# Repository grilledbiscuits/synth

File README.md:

# Fully Analog Synthesizer Passion Project

> This repository documents some of the work I have done starting in 2024 on
> this project.

I have tried to include as many schematics as possible. The schematics are
mainly just for documentation's sake, as it is rather difficult to simulate the
constantly-changing signals involved in these circuits. I haven't been able to
order a PCB for any of the modules designed here for cost-related issues but I
intend to keep working on this project to polish it to the best of my ability.

---

## Modules

Every module lives as its own sheet in the
[`synth-allmodules`](KiCAD/current-modules/synth-allmodules) KiCad project, with
the reference circuit it was designed from kept in
[`KiCAD/references`](KiCAD/references).

| Module | Based on | Reference |
| --- | --- | --- |
| ADSR | Kassutronics Precision ADSR (Eddy Bergman version) | [image](KiCAD/references/ADSR) |
| 8 Step Sequencer | [Eddy Bergman, 8 Step Sequencer v2.1](https://www.eddybergman.com/2019/12/synthesizer-build-part-8-8-step.html) | [image](KiCAD/references/8stepsequencer) |
| Bass | Thomas Henry, Bass++ | [image](KiCAD/references/bass) |
| LFO | Ken Stone, CGS58 Utility LFO | [image](KiCAD/references/LFO) |
| VCA | Thomas Henry, VCA-1 | [image](KiCAD/references/VCA) |
| VCF-1 | [Thomas Henry, VCF-1 State Variable Filter](https://www.eddybergman.com/2024/04/THVCF1statevariablefilter.html) | [image](KiCAD/references/VCF-1) |
| VCF-2 | [YuSynth, Steiner-Parker Diode Filter](https://www.eddybergman.com/2021/12/synthersizer-build-part-45-steiner.html) | [image](KiCAD/references/VCF-2) |
| VCO | Thomas Henry, X-4046 VCO | [image](KiCAD/references/VCO) |
| 808 Kick | [Juanito Moore, 808 Kick](https://www.eddybergman.com/2021/12/synthesizer-build-part-46-808-kick-for.html) | [image](KiCAD/references/808kick) |

## Repository Layout

```
KiCAD/
├── current-modules/
│   ├── synth-allmodules/   # main project, one sheet per module
│   └── 8stepsequencer/     # standalone sequencer project
├── references/             # reference schematics, one folder per module
├── Library/                # custom symbols and footprints
└── DEPRECATED/             # older designs, kept for reference
SPICE Models/
SLDWRKS (DEPRECATED)/
```

To open the schematics, load
`KiCAD/current-modules/synth-allmodules/synth-allmodules.kicad_pro` in KiCad 10.

---

## Core Concepts

This project is going to require us to expand our current level of
understanding of the following areas of electronic engineering:

- Soldering skills
- PCB design
- Analog Signals
- Schematics

## To-Do

- [x] Initialise a repo
- [x] Start up a README
- [ ] Update all schematics
- [ ] Start with CAD design of housings
- [ ] Add mute switches to the sequencer!
- [ ] Add an amplifier
- [ ] Plenty of other things, no doubt

## Possible Cool Features

These are just me spitballing crazy ideas. None of these really have anything
to do with the base project but it would be cool if we could look into these
somewhat:

- More LEDs for better visual feedback
- Some cheap screens to watch the signals
- Increased modularity and uniform housings
- More modules!
- Portable version???

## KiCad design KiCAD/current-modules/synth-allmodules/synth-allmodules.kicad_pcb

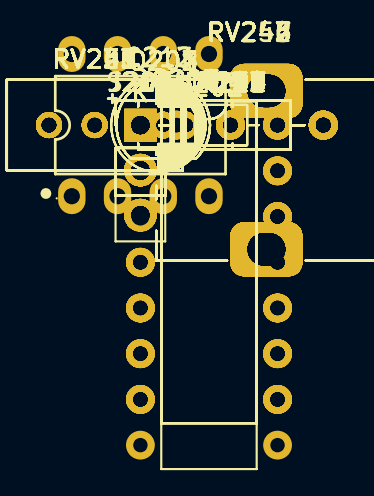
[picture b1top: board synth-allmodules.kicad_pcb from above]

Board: 2 copper layers, 93 parts (0 on the bottom side), 63 nets, no tracks yet.

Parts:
C201: 100p; C_Disc_D5.0mm_W2.5mm_P5.00mm
C202: 470p; C_Disc_D5.0mm_W2.5mm_P5.00mm
C203, C204, C205, C206, C207, C208, C209: 10n; C_Disc_D5.0mm_W2.5mm_P5.00mm
C210: 100n; C_Disc_D5.0mm_W2.5mm_P5.00mm
C211: 220n; C_Disc_D5.0mm_W2.5mm_P5.00mm
C212, C213: 10u; CP_Radial_D5.0mm_P2.00mm
D201, D202, D203: 1N4148; D_DO-35_SOD27_P7.62mm_Horizontal
J201: 1V/OCT; PinHeader_1x02_P2.54mm_Vertical
J202: EXP FM; PinHeader_1x02_P2.54mm_Vertical
J203: LIN FM; PinHeader_1x02_P2.54mm_Vertical
J204: HARD SYNC; PinHeader_1x02_P2.54mm_Vertical
J205: TRIANGLE; PinHeader_1x02_P2.54mm_Vertical
J206: RAMPOID; PinHeader_1x02_P2.54mm_Vertical
J207: SAW; PinHeader_1x02_P2.54mm_Vertical
J208: PWM; PinHeader_1x02_P2.54mm_Vertical
J209: SINE; PinHeader_1x02_P2.54mm_Vertical
J210: PULSE; PinHeader_1x02_P2.54mm_Vertical
J211: +12 / GND / -12; PinHeader_1x03_P2.54mm_Vertical
Q201, Q202, Q203, Q204, Q205: 2N3904; TO-92_Inline
R202, R203: 390R; R_Axial_DIN0207_L6.3mm_D2.5mm_P10.16mm_Horizontal
R204, R205, R206, R207: 1k; R_Axial_DIN0207_L6.3mm_D2.5mm_P10.16mm_Horizontal
R208, R210, R211, R212, R213: 2.2k; R_Axial_DIN0207_L6.3mm_D2.5mm_P10.16mm_Horizontal
R209: 2k; R_Axial_DIN0207_L6.3mm_D2.5mm_P10.16mm_Horizontal
R214: 4.7k; R_Axial_DIN0207_L6.3mm_D2.5mm_P10.16mm_Horizontal
R215, R216, R217: 10k; R_Axial_DIN0207_L6.3mm_D2.5mm_P10.16mm_Horizontal
R218, R219: 15k; R_Axial_DIN0207_L6.3mm_D2.5mm_P10.16mm_Horizontal
R220: 12k; R_Axial_DIN0207_L6.3mm_D2.5mm_P10.16mm_Horizontal
R221: 18k; R_Axial_DIN0207_L6.3mm_D2.5mm_P10.16mm_Horizontal
R222: 33k; R_Axial_DIN0207_L6.3mm_D2.5mm_P10.16mm_Horizontal
R224, R225, R226: 75k; R_Axial_DIN0207_L6.3mm_D2.5mm_P10.16mm_Horizontal
R227, R228, R229, R230, R231, R232, R233, R234, R235: 100k; R_Axial_DIN0207_L6.3mm_D2.5mm_P10.16mm_Horizontal
R248, R249: 120k; R_Axial_DIN0207_L6.3mm_D2.5mm_P10.16mm_Horizontal
R250, R251, R252: 220k; R_Axial_DIN0207_L6.3mm_D2.5mm_P10.16mm_Horizontal
R254: 1.5M; R_Axial_DIN0207_L6.3mm_D2.5mm_P10.16mm_Horizontal
R255: 2.2M; R_Axial_DIN0207_L6.3mm_D2.5mm_P10.16mm_Horizontal
R256: 3.3M; R_Axial_DIN0207_L6.3mm_D2.5mm_P10.16mm_Horizontal
RV201: 100R; Potentiometer_Bourns_3296W_Vertical
RV223: 50k; Potentiometer_Bourns_3296W_Vertical
RV236, RV237, RV238, RV239, RV240, RV241: 100k; Potentiometer_Bourns_3296W_Vertical
RV242, RV243, RV244, RV245, RV246, RV247: 100k; Potentiometer_Alps_RK09K_Single_Vertical
RV253: 500k; Potentiometer_Alps_RK09K_Single_Vertical
S201: AC/DC; PinHeader_1x02_P2.54mm_Vertical
U201: CD4046B; DIP-16_W7.62mm
U202: LF442; PDIP-8_L9.3-W6.4-P2.54-LS7.9-BL-1
U203, U204: TL074; DIP-14_W7.62mm

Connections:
+12V: C204.1, C206.1, C208.1, C210.1, C212.1, J211.1, R214.1, R216.1, R217.1, R254.1, RV238.1, RV243.1, RV244.1, RV247.1, U201.9, U201.14, U201.16, U202.8, U203.4, U204.4
-12V: C205.2, C207.2, C209.2, C213.2, J211.3, R221.2, RV240.1, RV243.3, RV244.3, RV247.3, U202.4, U203.11, U204.11
GND: C204.2, C205.1, C206.2, C207.1, C208.2, C209.1, C210.2, C212.2, C213.1, D203.2, J201.2, J202.2, J203.2, J204.2, J205.2, J206.2, J207.2, J208.2, J209.2, J210.2, J211.2, Q202.2, Q203.1, R202.2, R208.2, R210.2, R211.2, R219.2, R248.2, RV237.3, RV238.3, RV239.3, RV240.3, RV242.3, RV245.3, RV246.3, U201.8, U202.3, U202.5, U203.12, U204.12
unnamed: C202.2, R231.1
unnamed: D201.2, Q201.2, RV201.2
unnamed: D201.1, D202.2
unnamed: D202.1, R215.1
unnamed: D203.1, Q203.2, R231.2
unnamed: J201.1, R227.1
unnamed: J202.1, RV242.1
unnamed: C211.1, J203.1, S201.1
unnamed: C202.1, J204.1
unnamed: J205.1, R204.2
unnamed: J206.1, R205.2
unnamed: J207.1, R206.2
unnamed: J208.1, RV246.1
unnamed: J209.1, R207.2
unnamed: J210.1, R208.1, R213.2
unnamed: C201.1, Q201.3, R230.2, R254.2, U202.6
unnamed: Q201.1, Q202.1, R220.2
unnamed: Q202.3, U201.11
unnamed: Q203.3, R214.2, U201.3
unnamed: Q204.2, R210.1, RV241.2, RV241.3
unnamed: Q204.3, R216.2, R218.1, U204.6
unnamed: Q204.1, R203.1, RV223.1
unnamed: Q205.2, R211.1
unnamed: Q205.3, R217.2, R219.1, U204.5
unnamed: Q205.1, R203.2, RV223.3
unnamed: R202.1, RV201.3
unnamed: R204.1, R232.2, RV241.1, RV253.1, U203.8
unnamed: R206.1, R234.2, RV253.3, U203.14
unnamed: R207.1, R212.1, R218.2, U204.7
unnamed: R213.1, R255.2, U204.8
unnamed: R215.2, RV236.1
unnamed: R221.1, RV223.2
unnamed: R222.1, RV237.2
unnamed: R228.1, RV242.2
unnamed: R229.1, RV243.2
unnamed: R230.1, RV245.2
unnamed: R233.1, RV239.2
unnamed: R235.1, RV246.2
unnamed: R250.1, RV238.2
unnamed: R251.1, RV240.2
unnamed: R252.1, RV247.2
unnamed: R256.1, RV244.2
unnamed: C211.2, RV245.1, S201.2
unnamed: C203.1, U201.6, U203.5
unnamed: C203.2, U201.7, U203.3
unnamed: RV239.1, U201.4
unnamed: U201.2, U201.5
unnamed: R209.1, R227.2, R228.2, R229.2, R256.2, U202.2
unnamed: R209.2, RV201.1, U202.1
unnamed: C201.2, R220.1, RV236.2, RV236.3, U202.7
unnamed: R225.1, RV237.1, U203.1, U203.2
unnamed: R224.1, R226.1, U203.6, U203.7
unnamed: R224.2, R233.2, R248.1, U203.10
unnamed: R222.2, R232.1, R250.2, U203.9
unnamed: R225.2, R226.2, R234.1, R251.2, U203.13
unnamed: RV253.2, U204.3
unnamed: R205.1, U204.1, U204.2
unnamed: R212.2, R255.1, U204.10
unnamed: R249.2, U204.9, U204.14
unnamed: R235.2, R249.1, R252.2, U204.13

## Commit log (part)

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2026-04-05 V0.0.1
    Additions:
    - All existing files
    Updates:
    -None
    Removals:
    -None
2026-04-05 V0.0.2
    Additions:
    - None
    Updates:
    - README now says something
    Removals:
    - None
2026-04-13 First Commit With Murray On!
    Additions:
    - None
    Changes:
    - Better README
    - Added DEPRECATED labels on pretty much everything since we're starting again with some cleaner documentation
    Removals:
2026-04-14 New schematic!
    Additions:
    - New hierarchical schematic sheet
    - Mostly completed ADSR
    Changes:
    - None
    Removals:
2026-04-21 Sequencer Start
    Additions:
    - Added all components for sequencer schematic
    Changes:
    - None
    Removals:
    - None
2026-04-22 Mostly Finished Sequencer
    Additions:
    - Wired up sequencer except for IOs
    Changes:
    - None
    Removals:
    - None
2026-04-23 Sequencer Tweaks
    Additions:
    - Text IO labels
    Changes:
    - Replaced 2 related SPSTs with a DPST
    Removals:
    - None
2026-05-12 Added bass module
    Additions:
    - Bass module minus audio jacks
    Changes:
    - None
    Removals:
    - None
2026-05-13 VCA components
    Additions:
    - Added appropriate components for VCA module
    Changes:
    - None
    Removals:
    - None
2026-05-14 VCA wired minus jacks
    Additions:
    - Connected up the VCA circuit
    Changes:
    - None
    Removals:
    - None
2026-05-15 VCA IOs labelled
    Additions:
    - IO and potentiometer labels for VCA module
    Changes:
    - None
    Removals:
    - None
2026-05-19 Started LFO
    Additions:
    - Some LFO components
    Changes:
    - None
    Removals:
    - None
2026-05-21 More LFO Components
    Additions:
    - Some LFO components
    Changes:
    - None
    Removals:
    - None
2026-05-23 Added Remaining LFO Components
    Additions:
    - Remaining LFO components
    Changes:
    - None
    Removals:
    - None
2026-05-23 Initial Component Placement
    Additions:
    - None
    Changes:
    - Vague component placement for one of the LFOs. No values on components yet.
    Removals:
    - None
2026-05-23 Half Component Values
    Additions:
    - Half of the components' values have been assigned
    Changes:
    - None
    Removals:
    - None
2026-05-24 Other Half Placed
    Additions:
    - Second LFO module components placed and assigned values.
    - Decoupling caps
    Changes:
    - None
    Removals:
2026-05-24 Power Connected
    Additions:
    - None
    Changes:
    - uC power pins connected
    - Decoupling caps connected
    Removals:
2026-05-24 Wiring and Labelling Start
    Additions:
    - Output labels
    - uC function labels
    Changes:
    - Wired first LFO module
    Removals:
2026-05-24 Tweaks
    Additions:
    - Little bits remaining on first module
    Changes:
    - None
    Removals:
    - None
2026-05-25 Second LFO module wired
    Additions:
    - Connected components for second LFO module
    Changes:
    - None
    Removals:
    - None
2026-05-26 LFO Labels Complete
    Additions:
    - Remaining labels added for LFO module
    Changes:
    - None
    Removals:
    - None
2026-05-28 VCF-1 Components Placed
    Additions:
    - Basic components for VCF-1
    Changes:
    - None
    Removals:
    - None
2026-05-28 VCF-1 Component Placement
    Additions:
    - Most of the components for VCF-1 have been placed in the correct spots
    Changes:
    - None
    Removals:
    - None
2026-05-29 Added Power Caps
    Additions:
    - Decoupling caps have been placed but need connection, along with the rest of the circuit
    Changes:
    - None
    Removals:
    - None
2026-05-31 Started VCF-1 Connections
    Additions:
    - Connected some components on VCF
    Changes:
    - None
    Removals:
    - None
2026-06-02 Resumed ADSR
    Additions:
    - Annotated some of the ADSR and added some connections
    Changes:
    - None
    Removals:
    - None
2026-06-03 ADSR Work (Needs cap values)
    Additions:
    - Remaining ADSR annotations
    - Remaining ADSR connections
    - Remaining ADSR components
    Changes:
    - None
2026-06-05 Tweaks
    Idk just small stuff
2026-06-09 Label changes
